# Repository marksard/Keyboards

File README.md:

# Keyboards

This repository is warehouse of my keyboard architecture.  

## About Firmware

[Release firmware](https://github.com/marksard/qmk_firmware_hex/releases)  
[Keymap editing web service REMAP](https://remap-keys.app/)  

## WARNING
<b>Note that for these keyboards, the design is older and also less likely to support the latest firmware and architecture.<b>  
<b>Also, KICAD files may be incomplete, they are not going to be perfect.<b>

## Rhymestone

### About Rhymestone

The Rhymestone is 40-key (40%) ortholinear keyboard. It is based on [The crkbd](https://github.com/foostan/crkbd) and [The Helix keyboard](https://github.com/MakotoKurauchi/helix). Thank you so much makoto kurauchi-san and foostan-san.😊  

[Build guide](./rhymestone/documents/rhymestone_buildguide.md)  
[Firmware](https://github.com/marksard/qmk_firmware/tree/own_build/keyboards/marksard/)  
[Hardware data](https://github.com/marksard/Keyboards/tree/master/rhymestone/)  

## Treadstone48

rev1  

rev2  

### About Treadstone48

The Treadstone48 is 47 or 48-key (50%) Symmetric staggered keyboard. It is based on the Rhymestone. Therefore, The Rhymestone can connect to the Treadstone48 as Numpad or lefthand keyboard. (rev1 only)  

This Symmetrical Staggered is designed to be easy to use in a natural posture and easy for your fingers to reach.  
And more one topic, this key arrangement can use general ansi 104 keycaps.

[Build guide (rev.2)](./treadstone48/documents/treadstone48rev2_buildguide.md)  

[Build guide](./treadstone48/documents/treadstone48_buildguide.md)  
[Build guide (En)](./treadstone48/documents/treadstone48_buildguide_en.md)  
[Firmware](https://github.com/qmk/qmk_firmware/tree/master/keyboards/treadstone48)  
[Hardware data](https://github.com/marksard/Keyboards/tree/master/treadstone48/)  
[About Treadstone48](https://marksard.github.io/2018/12/17/about-treadstone48/)  
[Case design sample](https://marksard.github.io/2019/04/11/wood-case/)  

## Stonehenge30 (deprecated)

### About Stonehenge30

The Stonehenge30 is 30-key (30%) Symmetric staggered keyboard. It is based on the Treadstone48. And it is thumb-less (not use thumb) keyboard of prototype.  

[Build guide](./stonehenge30/documents/stonehenge30_buildguide.md)  
[Firmware](https://github.com/marksard/qmk_firmware/tree/own_build/keyboards/marksard/)  
[Hardware data](https://github.com/marksard/Keyboards/tree/master/stonehenge30/)  
[About Stonehenge30](https://marksard.github.io/2019/02/13/make-stonehenge30/)  
[Case design sample](https://marksard.github.io/2019/04/11/wood-case/)  

## Treadstone32

rev1  

lite  

### About Treadstone32

The Treadstone32 is 32-key (30%) Symmetric staggered keyboard. It is based on the Treadstone48 and the Stonehenge30.  
This keyboard is removing dedicated modifire-key from the Treadstone48 for more compact. But 2 thumb-key is left same as Treadtone48.  

[Build guide (lite)](./treadstone32/documents/treadstone32lite_buildguide.md)  
[Build guide](./treadstone32/documents/treadstone32_buildguide.md)  

[Build guide (En)](./treadstone32/documents/treadstone32_buildguide_en.md)  
[Firmware](https://github.com/qmk/qmk_firmware/tree/master/keyboards/treadstone32)  
[Hardware data](https://github.com/marksard/Keyboards/tree/master/treadstone32/)  
[About Treadstone32](https://marksard.github.io/2019/04/25/about-treadstone32/)  

## Treadstone60

### About Treadstone60

The Treadstone60 is 59-62key (60%) Symmetric staggered keyboard. It is based on the Treadstone48 and the Treadstone32.  

[Build guide](./treadstone60/documents/treadstone60_buildguide.md)  

[Firmware](https://github.com/marksard/qmk_firmware/tree/own_build/keyboards/marksard/)  
[About Treadstone60](https://marksard.github.io/2019/12/13/about-treadstone60/)  

## Leftover30

### About Leftover30

The Leftover30 is 34-36key (30%) Row staggered keyboard. This project was created by marksard, yohewi and hdbx.  

[Build guide](./leftover30/documents/leftover30_buildguide.md)  

[Firmware](https://github.com/marksard/qmk_firmware/tree/own_build/keyboards/marksard/)  

## Troubleshooting

[Troubleshooting](./troubleshooting.md)

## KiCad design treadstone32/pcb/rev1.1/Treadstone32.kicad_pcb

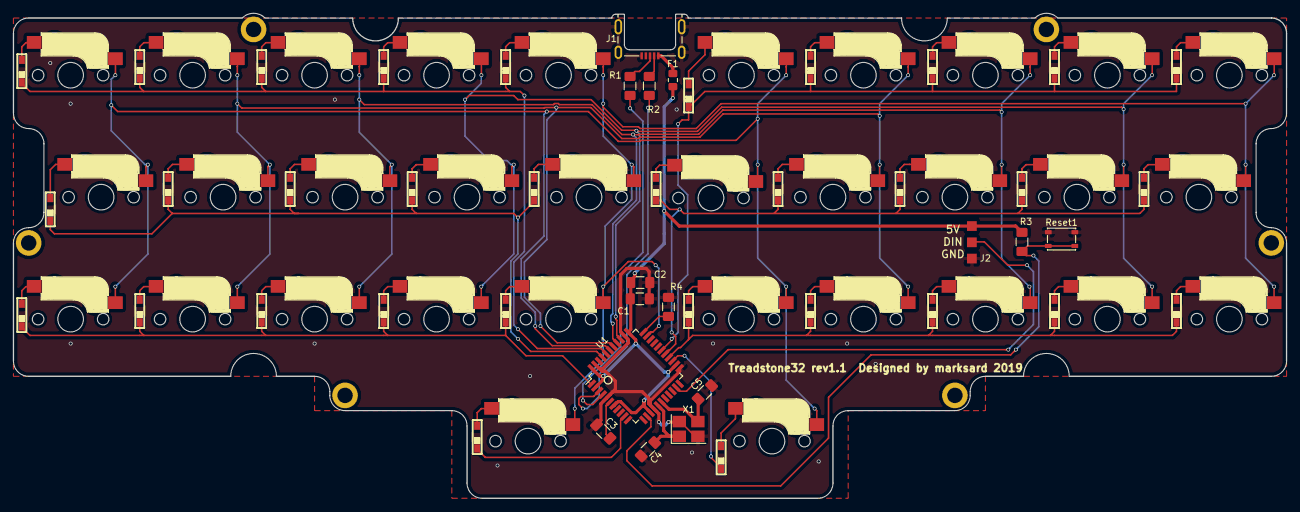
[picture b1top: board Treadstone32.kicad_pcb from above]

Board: 2 copper layers, 198.8 x 75.8 mm, 79 parts (0 on the bottom side), 58 nets.

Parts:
C1: 0.1uF; C_1206_3216Metric_Pad1.42x1.75mm_HandSolder
C2, C3: 1uF; C_1206_3216Metric_Pad1.42x1.75mm_HandSolder
C4, C5: 22pF; C_1206_3216Metric_Pad1.42x1.75mm_HandSolder
D1, D2, D3, D4, D5, D6, D7, D8, D9, D10, D11, D12, D13, D14, D15, D16, D17, D18, D19, D20, D21, D22, D23, D24, D25, D26, D27, D28, D29, D30, D31, D32: D; D3_SMD_only_front
F1: 500mA; Fuse_0805_2012Metric_Pad1.15x1.40mm_HandSolder
J1: USB_mini_micro_B; MOLEX_47642-0001_HandSoldering_cuts
J2: Conn_01x03; StripLED_front
R1, R2: 22; R_1206_3216Metric_Pad1.42x1.75mm_HandSolder
R3, R4: 10k; R_1206_3216Metric_Pad1.42x1.75mm_HandSolder
Reset1: Reset; SW_SPST_PTS810
SW1, SW2, SW3, SW4, SW5, SW6, SW7, SW8, SW9, SW10, SW11, SW12, SW13, SW14, SW15, SW16, SW17, SW18, SW19, SW20, SW21, SW22, SW23, SW24, SW25, SW26, SW27, SW28, SW29, SW30, SW31, SW32: SW_PUSH; CherryMX_Hotswap_front
U1: ATMEGA32U4; TQFP-44_10x10mm_P0.8mm
X1: 16MHz; Crystal_SMD_3225-4Pin_3.2x2.5mm_HandSoldering

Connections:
GND: C1.2, C2.2, C3.1, C4.2, C5.2, J1.5, J1.6, J2.1, R4.2, Reset1.1, U1.5, U1.15, U1.23, U1.35, U1.43, X1.2, X1.4
LED: J2.2, U1.21
unnamed: C3.2, U1.6
unnamed: C4.1, U1.16, X1.1
unnamed: C5.1, U1.17, X1.3
unnamed: D1.2, SW1.2
unnamed: D2.2, SW2.2
unnamed: D3.2, SW3.2
unnamed: D4.2, SW4.2
unnamed: D5.2, SW5.2
unnamed: D6.2, SW6.2
unnamed: D7.2, SW7.2
unnamed: D8.2, SW8.2
unnamed: D9.2, SW9.2
unnamed: D10.2, SW10.2
unnamed: D11.2, SW11.2
unnamed: D12.2, SW12.2
unnamed: D13.2, SW13.2
unnamed: D14.2, SW14.2
unnamed: D15.2, SW15.2
unnamed: D16.2, SW16.2
unnamed: D17.2, SW17.2
unnamed: D18.2, SW18.2
unnamed: D19.2, SW19.2
unnamed: D20.2, SW20.2
unnamed: D21.2, SW21.2
unnamed: D22.2, SW22.2
unnamed: D23.2, SW23.2
unnamed: D24.2, SW24.2
unnamed: D25.2, SW25.2
unnamed: D26.2, SW26.2
unnamed: D27.2, SW27.2
unnamed: D28.2, SW28.2
unnamed: D29.2, SW29.2
unnamed: D30.2, SW30.2
unnamed: D31.2, SW31.2
unnamed: D32.2, SW32.2
unnamed: F1.1, J1.1
unnamed: J1.2, R2.1
unnamed: J1.3, R1.1
unnamed: R1.2, U1.4
unnamed: R2.2, U1.3
unnamed: R3.2, Reset1.2, U1.13
unnamed: R4.1, U1.33
VCC: C1.1, C2.1, F1.2, J2.3, R3.1, U1.2, U1.7, U1.14, U1.24, U1.34, U1.44
col0: SW1.1, SW2.1, SW3.1, SW17.1, SW18.1, SW19.1, SW20.1, U1.39
col1: SW4.1, SW5.1, SW6.1, SW21.1, SW22.1, SW23.1, U1.38
col2: SW7.1, SW8.1, SW9.1, SW24.1, SW25.1, SW26.1, U1.37
col3: SW10.1, SW11.1, SW12.1, SW27.1, SW28.1, SW29.1, U1.36
col4: SW13.1, SW14.1, SW15.1, SW16.1, SW30.1, SW31.1, SW32.1, U1.32
row0: D1.1, D4.1, D7.1, D10.1, D13.1, U1.40
row1: D2.1, D5.1, D8.1, D11.1, D14.1, U1.41
row2: D3.1, D6.1, D9.1, D12.1, D15.1, U1.1
row3: D16.1, U1.10
row4: D17.1, D21.1, D24.1, D27.1, D30.1, U1.28
row5: D18.1, D22.1, D25.1, D28.1, D31.1, U1.27
row6: D19.1, D23.1, D26.1, D29.1, D32.1, U1.26
row7: D20.1, U1.25

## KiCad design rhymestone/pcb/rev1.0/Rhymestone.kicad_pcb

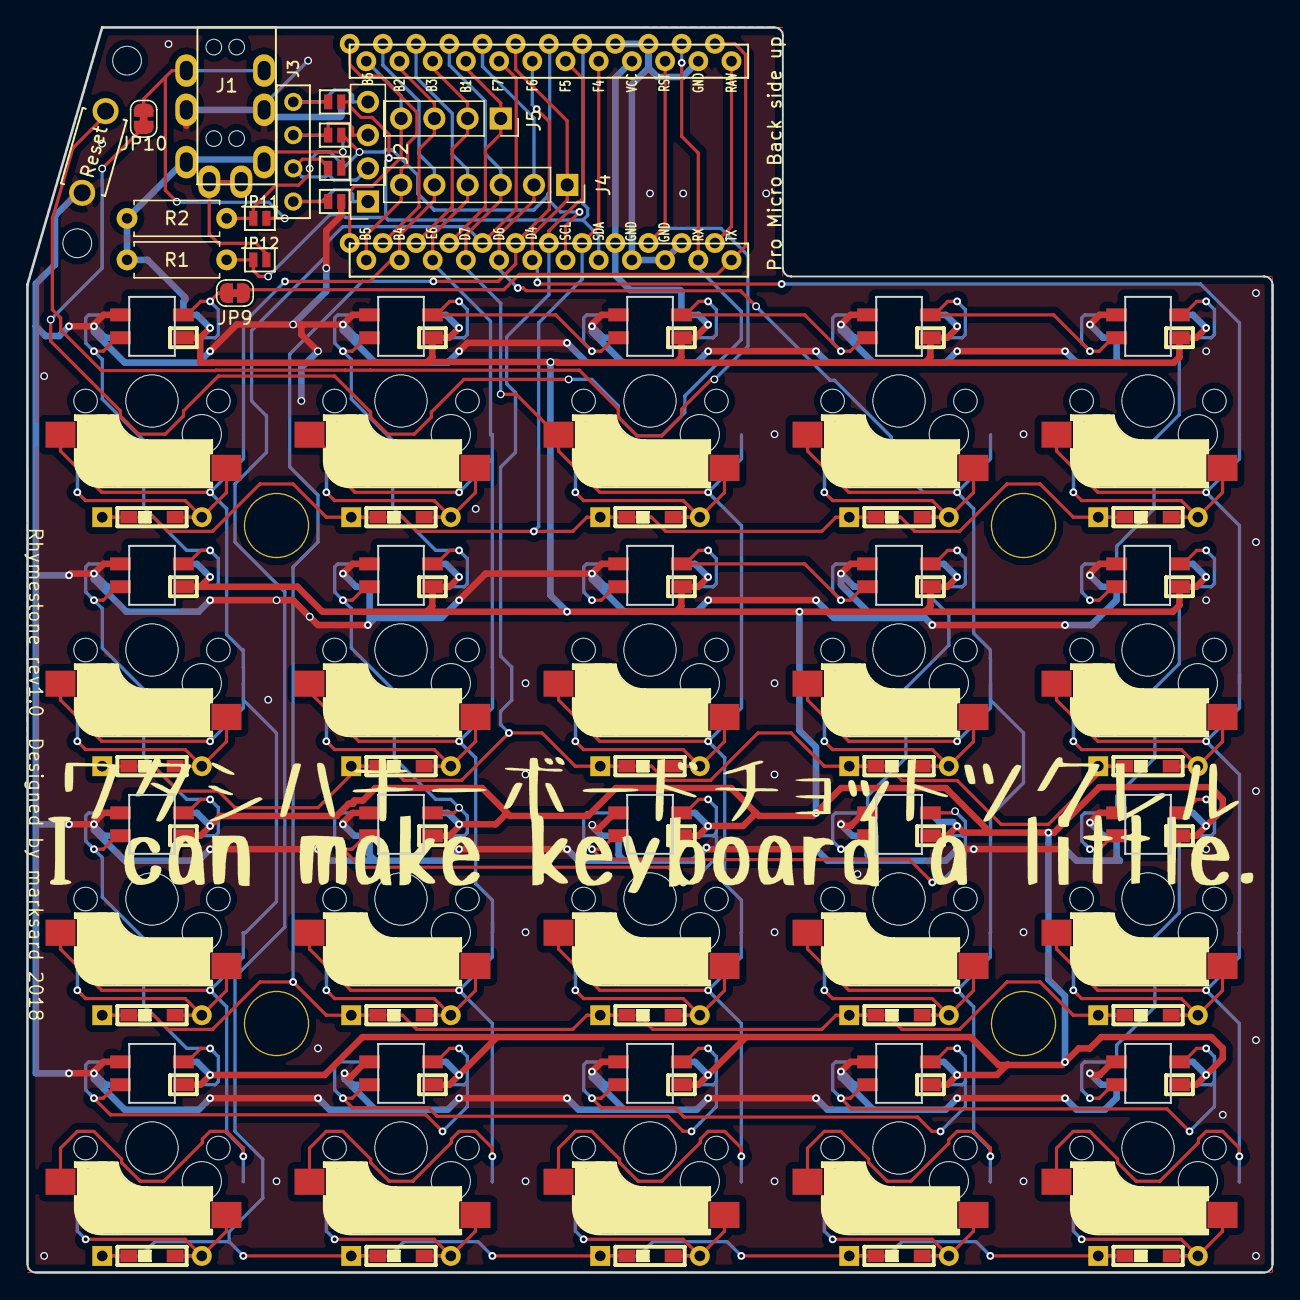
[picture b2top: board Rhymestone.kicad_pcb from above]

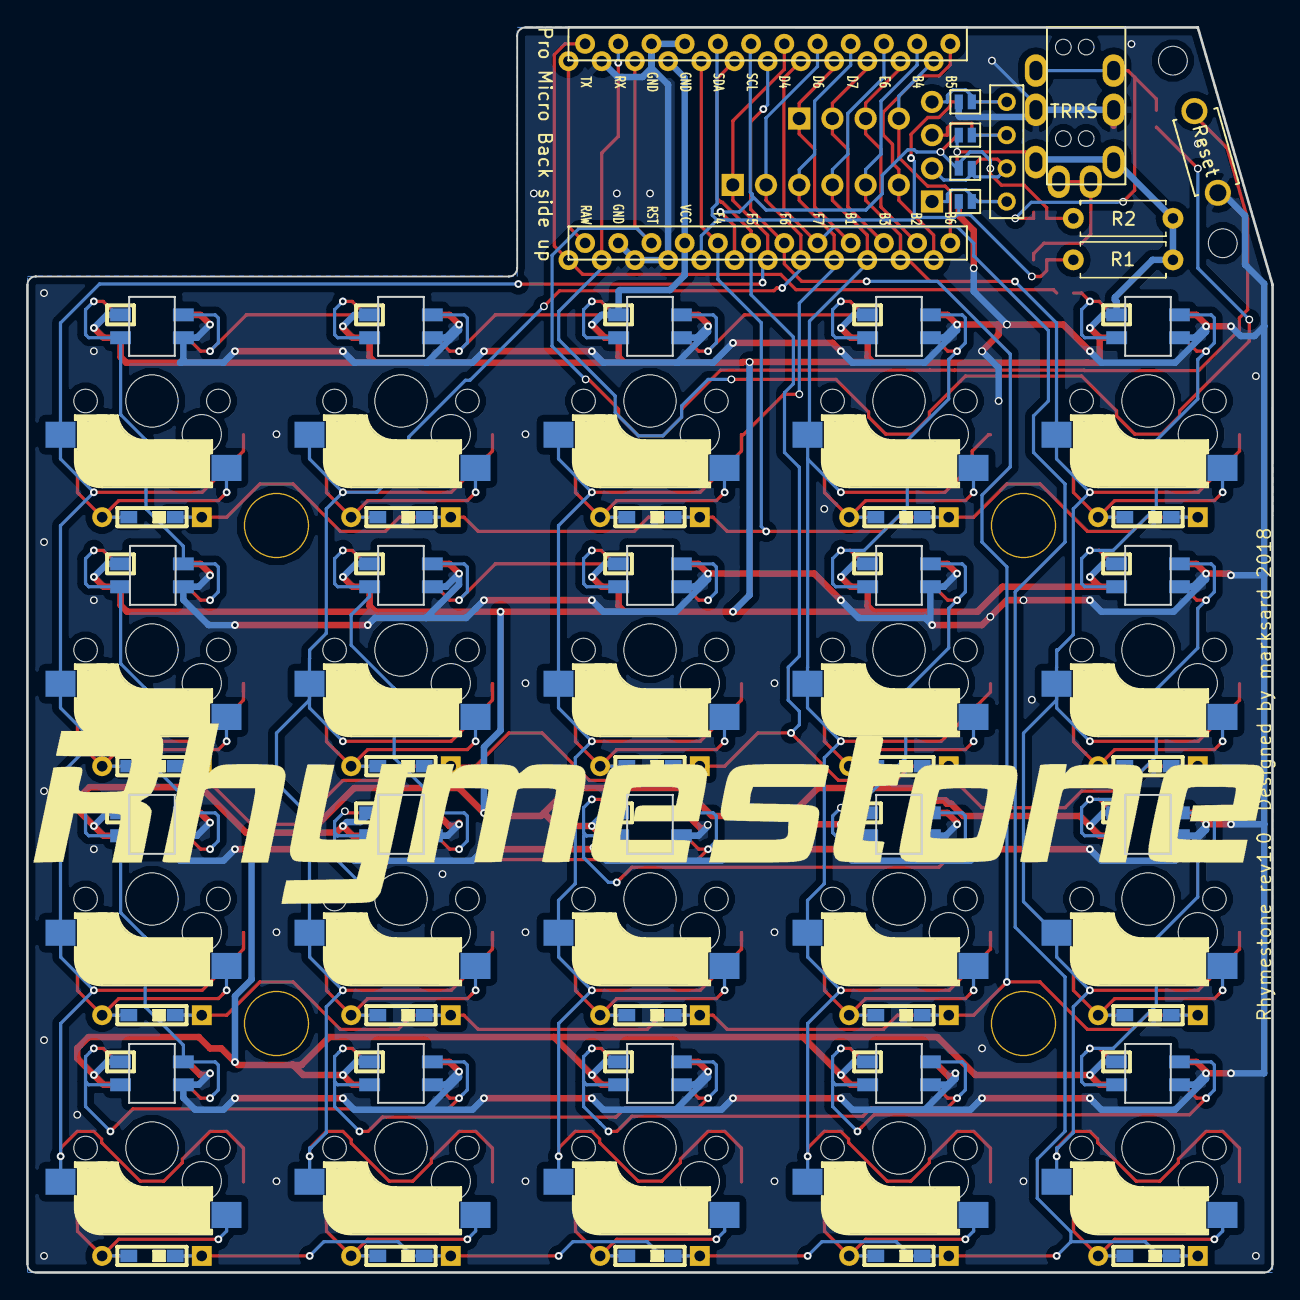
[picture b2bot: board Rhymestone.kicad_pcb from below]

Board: 2 copper layers, 95.3 x 95.3 mm, 87 parts (4 on the bottom side), 67 nets.

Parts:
D1, D2, D3, D4, D5, D6, D7, D8, D9, D10, D11, D12, D13, D14, D15, D16, D17, D18, D19, D20: D; D3_SMD
J1: MJ-4PP-9
J2: AUX; PinSocket_1x04_P2.54mm_Vertical
J3: OLED
J4: Columns; PinSocket_1x06_P2.54mm_Vertical
J5: Rows; PinSocket_1x04_P2.54mm_Vertical
JP1, JP2, JP3, JP4, JP5, JP6, JP7, JP8: Jumper
JP9: LED; SolderJumper-2_P1.3mm_Bridged_RoundedPad1.0x1.5mm
JP10: DataJP; SolderJumper-2_P1.3mm_Bridged_RoundedPad1.0x1.5mm
JP11: SDLJP; Jumper
JP12: SDAJP; Jumper
L1, L2, L3, L4, L5, L6, L7, L8, L9, L10, L11, L12, L13, L14, L15, L16, L17, L18, L19, L20: SK6812MINI; SK6812MINI_rev
R1, R2: R; R_TH
RSW1: Reset; ResetSW
SW1, SW2, SW3, SW4, SW5, SW6, SW7, SW8, SW9, SW10, SW11, SW12, SW13, SW14, SW15, SW16, SW17, SW18, SW19, SW20: SW_PUSH; CherryMX_Hotswap
U1: ProMicro; ProMicro_v2
h1, h2, h3, h4: hole; LEGO_HOLE
h7, h8: hole; LEGO_HOLE2

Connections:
GND: J1.C, JP1.1, JP8.1, L1.2, L2.2, L3.2, L4.2, L5.2, L6.2, L7.2, L8.2, L9.2, L10.2, L11.2, L12.2, L13.2, L14.2, L15.2, L16.2, L17.2, L18.2, L19.2, L20.2, RSW1.2, U1.3, U1.4, U1.23
LED: JP9.2, U1.1
unnamed: D1.2, SW1.2
unnamed: D2.2, SW2.2
unnamed: D3.2, SW3.2
unnamed: D4.2, SW4.2
unnamed: D5.2, SW5.2
unnamed: D6.2, SW6.2
unnamed: D7.2, SW7.2
unnamed: D8.2, SW8.2
unnamed: D9.2, SW9.2
unnamed: D10.2, SW10.2
unnamed: D11.2, SW11.2
unnamed: D12.2, SW12.2
unnamed: D13.2, SW13.2
unnamed: D14.2, SW14.2
unnamed: D15.2, SW15.2
unnamed: D16.2, SW16.2
unnamed: D17.2, SW17.2
unnamed: D18.2, SW18.2
unnamed: D19.2, SW19.2
unnamed: D20.2, SW20.2
unnamed: J1.A, JP12.2
unnamed: J1.B, JP10.2, JP11.2
unnamed: J2.1, J3.1, JP1.2, JP5.2
unnamed: J2.2, J3.2, JP2.2, JP6.2
unnamed: J2.3, J3.3, JP3.2, JP7.2
unnamed: J2.4, J3.4, JP4.2, JP8.2
unnamed: JP9.1, L1.3
unnamed: L1.1, L2.3
unnamed: L2.1, L3.3
unnamed: L3.1, L4.3
unnamed: L4.1, L5.3
unnamed: L5.1, L6.3
unnamed: L6.1, L7.3
unnamed: L7.1, L8.3
unnamed: L8.1, L9.3
unnamed: L10.1, L11.3
unnamed: L9.1, L10.3
unnamed: L11.1, L12.3
unnamed: L12.1, L13.3
unnamed: L13.1, L14.3
unnamed: L14.1, L15.3
unnamed: L15.1, L16.3
unnamed: L16.1, L17.3
unnamed: L17.1, L18.3
unnamed: L18.1, L19.3
unnamed: L19.1, L20.3
SCL: JP3.1, JP6.1, JP11.1, R2.1, U1.6
SDA: JP4.1, JP5.1, JP12.1, R1.2, U1.5
VCC: J1.D, JP2.1, JP7.1, L1.4, L2.4, L3.4, L4.4, L5.4, L6.4, L7.4, L8.4, L9.4, L10.4, L11.4, L12.4, L13.4, L14.4, L15.4, L16.4, L17.4, L18.4, L19.4, L20.4, R1.1, R2.2, U1.21
col0: J4.1, SW1.1, SW2.1, SW3.1, SW4.1, U1.7
col1: J4.2, SW5.1, SW6.1, SW7.1, SW8.1, U1.8
col2: J4.3, SW9.1, SW10.1, SW11.1, SW12.1, U1.9
col3: J4.4, SW13.1, SW14.1, SW15.1, SW16.1, U1.10
col4: J4.5, SW17.1, SW18.1, SW19.1, SW20.1, U1.11
col5: J4.6, U1.12
data: JP10.1, U1.2
reset: RSW1.1, U1.22
row0: D1.1, D5.1, D9.1, D13.1, D17.1, U1.20
row1: D2.1, D6.1, D10.1, D14.1, D18.1, U1.19
row2: D3.1, D7.1, D11.1, D15.1, D19.1, U1.18
row3: D4.1, D8.1, D12.1, D16.1, D20.1, U1.17
row4: J5.1, U1.16
row5: J5.2, U1.15
row6: J5.3, U1.14
row7: J5.4, U1.13

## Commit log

2018-12-18 Rhymestone: Add some project files Treadstone48: Add some project files
2018-12-18 rhymestone: update buildguide
2018-12-19 readme: add images
2018-12-19 readme: update article
2018-12-19 readme: update
2018-12-19 rhymestone: add images
2018-12-19 rhymestone:update buildguide
2018-12-19 rhymestone: add keymap png
2018-12-20 rhymestone: update
2018-12-20 rhymestone: add led
2018-12-20 rhymestone: add diode section
2018-12-21 treadstone48: update buildguide
2018-12-21 Rhymestone/Treadstone48: update
2018-12-23 treadstone48: add images
2018-12-25 treadstone48: update
2019-01-02 add keymap link
2019-01-11 rhyme/tread: update buildguide
2019-01-16 treadstone48: add document of when connect rhymestone
2019-01-16 treadstone48: add about oled rules.mk
2019-01-29 treadstone48: added woodcase cut file
2019-01-31 add troubleshooting.md
2019-01-31 troubleshooting: update
2019-02-01 rhymestone: added pcb project
2019-02-02 stonehenge30: added pcb data and case data
2019-02-02 stonehenge30: move directory
2019-02-03 stonehenge30: fixed led line.
2019-02-04 all: update and add: case and plate file
2019-02-05 stonehenge30: add buildguide
2019-02-05 stonehenge30: update buildguide
2019-02-05 Add images
2019-02-06 stonehenge30: add images
2019-02-06 stonehenge30: update
2019-02-06 add case readme
2019-02-12 Fixed issue #1
2019-02-12 stonehenge30: update case
2019-02-13 stonehenge30: add pcbmount
2019-02-26 stonehenge30: fixed case data
2019-03-05 rhymestone: add mount plate in case data
2019-03-12 fixed a little.
2019-03-14 all document update
2019-04-05 treadstone48: update qmk directory
2019-04-16 Keyboads: add about.
2019-04-16 Add about Treadstone32
2019-04-16 Treadstone32: add buildguide first commit
2019-04-16 treadstone32: update readme
2019-04-20 treadstone32: add contents
2019-04-21 treadstone32:update photo
2019-04-24 treadstone32: update buildguide
2019-04-25 treadstone32:update
2019-05-06 treadstone32:update buildguide
2019-05-06 treadstone32: add hex file
2019-05-20 toppage: Update link
2019-05-20 toppeage: update
2019-05-20 treadstone48: update build guide
2019-06-06 Treadstone48: Add pcb data. Enjoy!
2019-06-28 Treadstone48: add englisgh build guide
2019-07-08 treadstone48: update include parts of kit.
2019-07-24 treadstone48: added pcb rev1.3
2019-07-24 treadstone32: added pcb rev1.1
2019-07-24 treadstone32: added case data
2019-07-24 index: update
2019-07-24 treastone48: update buildguide
2019-07-24 treastone32: update buildguide
2019-07-29 treadstone32: remove old data and rename case file
2019-08-09 treadstone32: add engish build guide
2019-08-09 treadstone48: modified
2019-08-20 treadstone32: add case photos
2020-04-07 Added treadstone32lite and treadstone48rev2 build guide(WIP)
2020-05-08 [treadstone48]update build guide for rev1 and rev2 And refactor some picture.
2020-05-08 [treadstone48]update
2020-05-08 remove hex
2020-05-08 [treadstone32lite]update build guide
2020-05-09 [treadstone32]update buildguide
2020-05-10 [treadstone32]fixed buildguide
2020-08-04 [treadstone60]add treadstone60 build guide
2020-08-23 [leftover30]add new project
2020-08-23 [leftover30]add pics
2020-08-24 [leftover30] fixed embeded youtube link
2020-08-25 [leftover30]update
2020-08-27 [lifeover30]update
2020-08-31 [leftover30]add side acrylic plate
2020-09-04 Re-create the chapters describing qmk and promicro.
2020-09-19 [leftover30]update buildguide
2020-09-24 [leftover30]fixed
2021-03-08 updated writing firmware procedure
2021-03-10 fixed url link
2021-03-10 add desc keymap
